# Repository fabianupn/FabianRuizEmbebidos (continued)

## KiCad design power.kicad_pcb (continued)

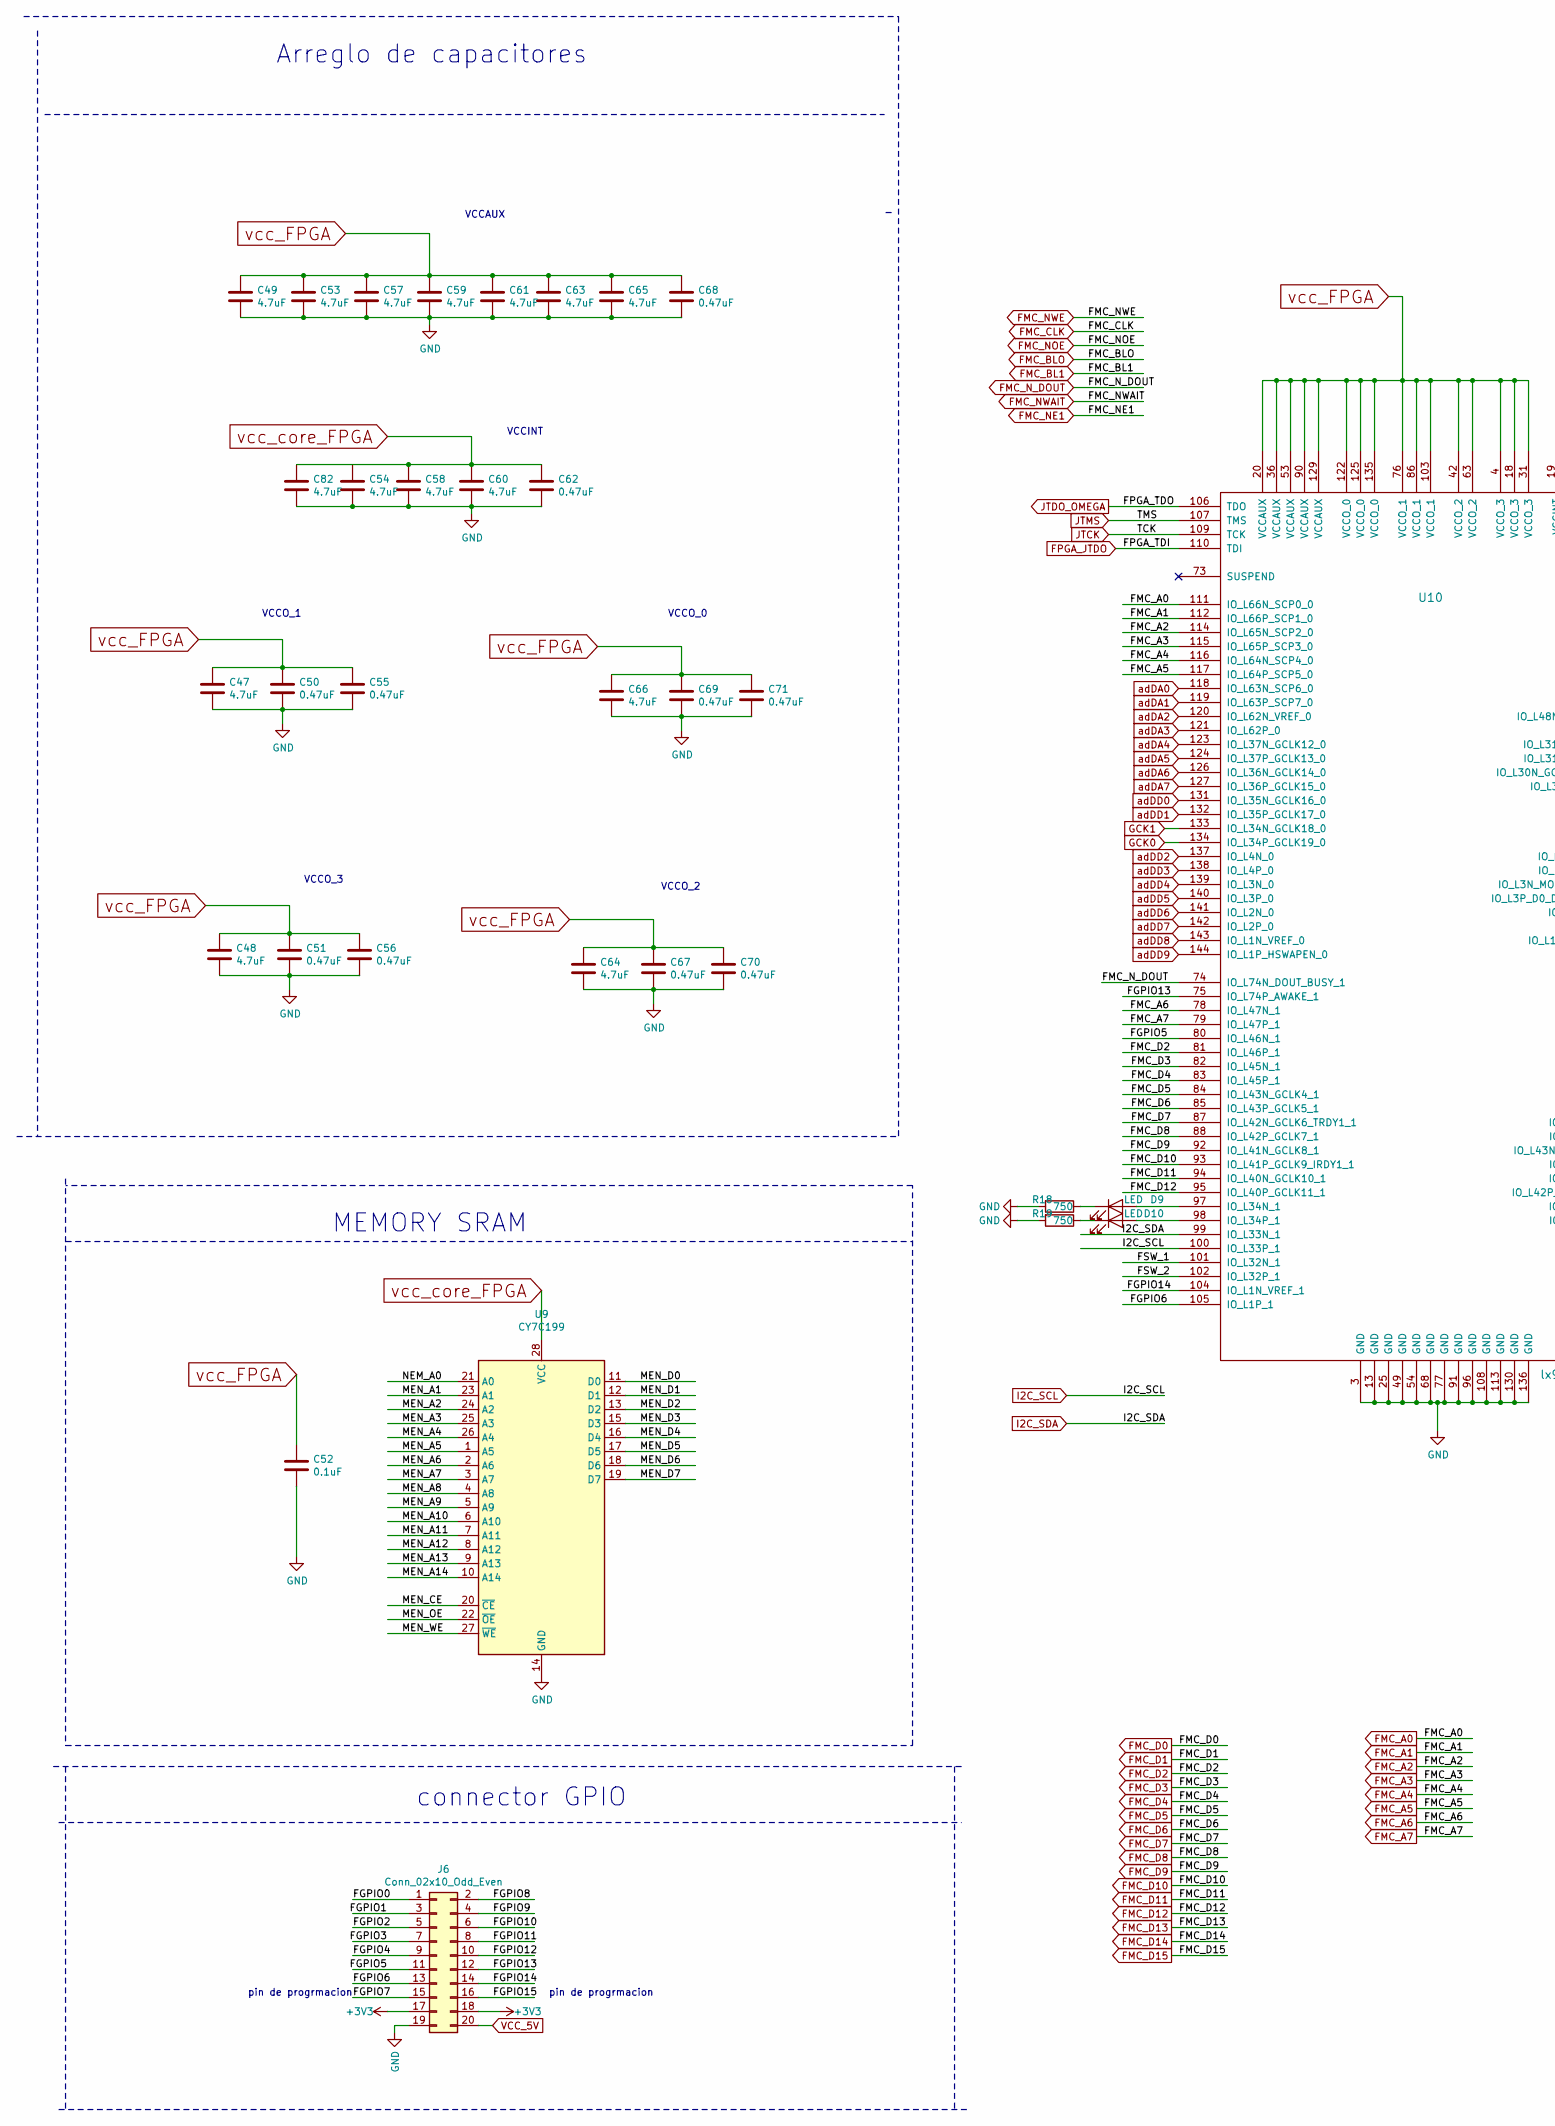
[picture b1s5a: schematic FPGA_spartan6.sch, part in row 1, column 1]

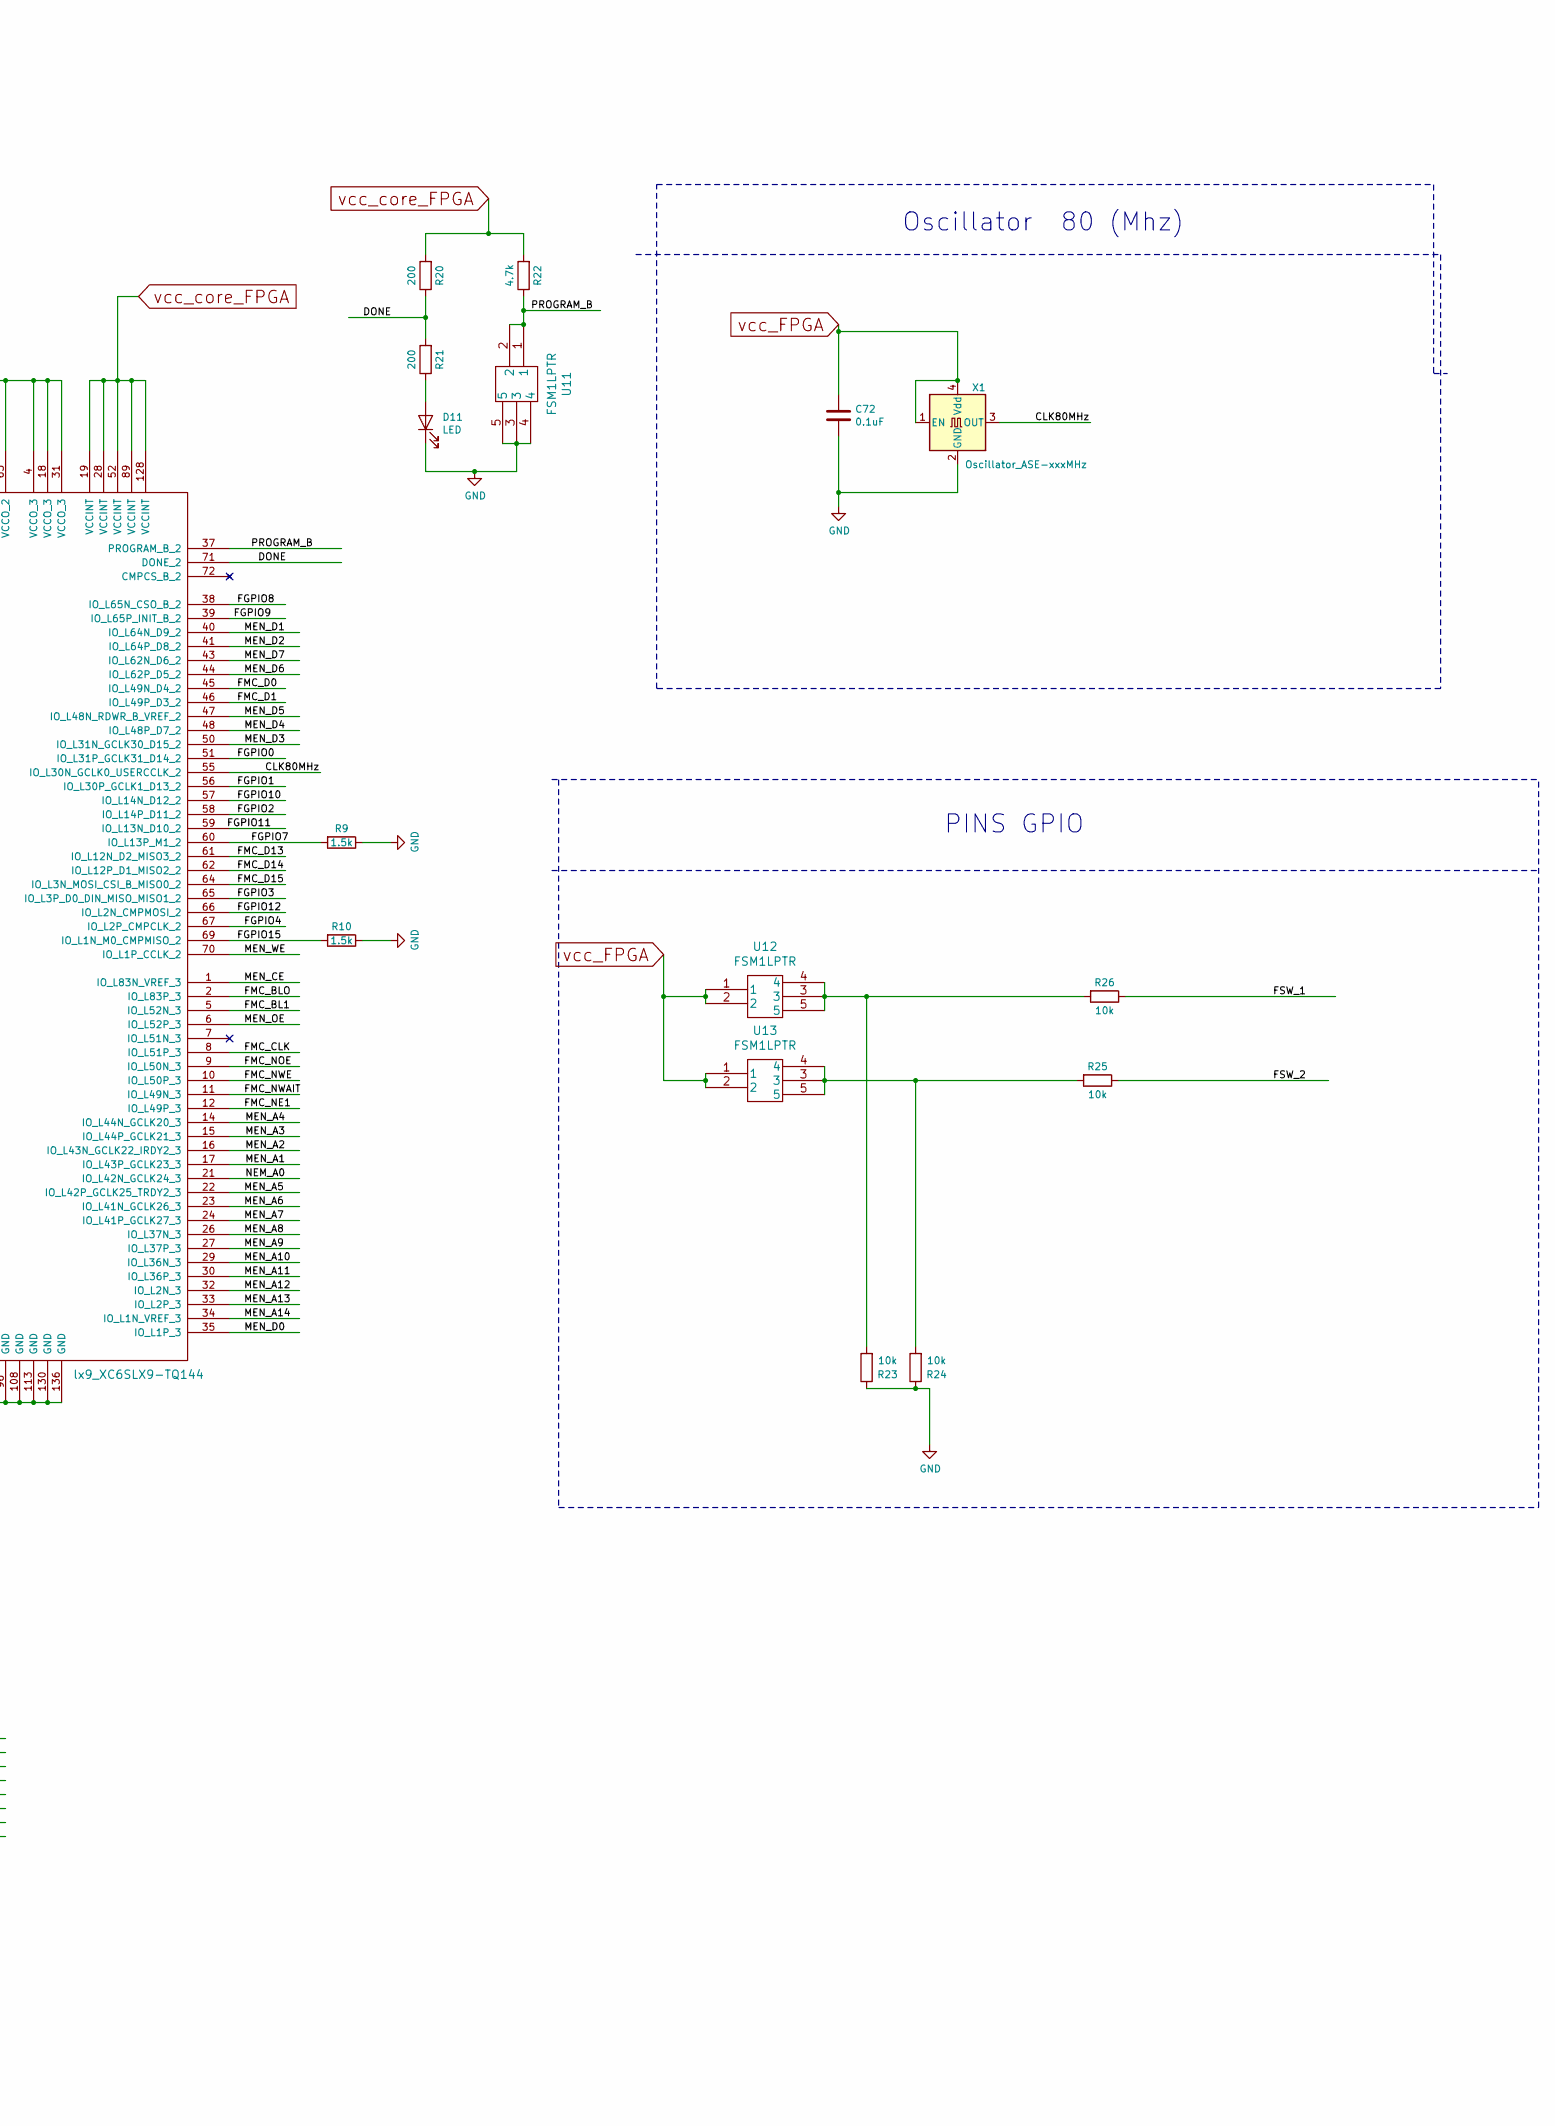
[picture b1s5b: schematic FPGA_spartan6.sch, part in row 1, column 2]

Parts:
C47, C48, C49, C53, C54, C57, C58, C59, C60, C61, C63, C64, C65, C66, C82: 4.7uF; C_0603_1608Metric_Pad1.05x0.95mm_HandSolder
C50, C51, C55, C56, C62, C67, C68, C69, C70, C71: 0.47uF; C_0603_1608Metric_Pad1.05x0.95mm_HandSolder
C52, C72: 0.1uF; C_0603_1608Metric_Pad1.05x0.95mm_HandSolder
D9, D10: LED; LED_0603_1608Metric_Pad1.05x0.95mm_HandSolder; digikey 160-1436-1-ND rojo
D11: LED; LED_0603_1608Metric_Pad1.05x0.95mm_HandSolder; digikey 160-1445-1-ND Naranja
J6: Conn_02x10_Odd_Even; PinHeader_2x10_P2.54mm_Vertical; digikey S6106-ND
R9, R10: 1.5k; R_0603_1608Metric_Pad1.05x0.95mm_HandSolder
R18, R19: 750; R_0603_1608Metric_Pad1.05x0.95mm_HandSolder
R20, R21: 200; R_0603_1608Metric_Pad1.05x0.95mm_HandSolder
R22: 4.7k; R_0603_1608Metric_Pad1.05x0.95mm_HandSolder
R23, R24, R25, R26: 10k; R_0603_1608Metric_Pad1.05x0.95mm_HandSolder
U9: CY7C199; TSOP-I-28_11.8x8mm_P0.55mm; digikey 428-2013-ND
U10: lx9_XC6SLX9-TQ144; LQFP-144_20x20mm_P0.5mm; digiker 122-1745-ND
U11, U12, U13: FSM1LPTR; digikey 450-1756-1-ND
X1: Oscillator_ASE-xxxMHz; Oscillator_SMD_Abracon_ASE-4Pin_3.2x2.5mm_HandSoldering; digikey 535-11114-1-ND

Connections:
/FPGA_spartan6/CLK80MHz: U10.55 (IO_L30N_GCLK0_USERCCLK_2), X1.3 (OUT)
/FPGA_spartan6/DONE: R20.1, R21.2, U10.71 (DONE_2)
/FPGA_spartan6/FGPIO0: J6.1, U10.51 (IO_L31P_GCLK31_D14_2)
/FPGA_spartan6/FGPIO1: J6.3, U10.56 (IO_L30P_GCLK1_D13_2)
/FPGA_spartan6/FGPIO2: J6.5, U10.58 (IO_L14P_D11_2)
/FPGA_spartan6/FGPIO3: J6.7, U10.65 (IO_L3P_D0_DIN_MISO_MISO1_2)
/FPGA_spartan6/FGPIO4: J6.9, U10.67 (IO_L2P_CMPCLK_2)
/FPGA_spartan6/FGPIO5: J6.11, U10.80 (IO_L46N_1)
/FPGA_spartan6/FGPIO6: J6.13, U10.105 (IO_L1P_1)
/FPGA_spartan6/FGPIO7: J6.15, R9.2, U10.60 (IO_L13P_M1_2)
/FPGA_spartan6/FGPIO8: J6.2, U10.38 (IO_L65N_CSO_B_2)
/FPGA_spartan6/FGPIO9: J6.4, U10.39 (IO_L65P_INIT_B_2)
/FPGA_spartan6/FGPIO10: J6.6, U10.57 (IO_L14N_D12_2)
/FPGA_spartan6/FGPIO11: J6.8, U10.59 (IO_L13N_D10_2)
/FPGA_spartan6/FGPIO12: J6.10, U10.66 (IO_L2N_CMPMOSI_2)
/FPGA_spartan6/FGPIO13: J6.12, U10.75 (IO_L74P_AWAKE_1)
/FPGA_spartan6/FGPIO14: J6.14, U10.104 (IO_L1N_VREF_1)
/FPGA_spartan6/FGPIO15: J6.16, R10.2, U10.69 (IO_L1N_M0_CMPMISO_2)
/FPGA_spartan6/FSW_1: R26.1, U10.101 (IO_L32N_1)
/FPGA_spartan6/FSW_2: R25.1, U10.102 (IO_L32P_1)
/FPGA_spartan6/MEN_A1: U9.23 (A1), U10.17 (IO_L43P_GCLK23_3)
/FPGA_spartan6/MEN_A2: U9.24 (A2), U10.16 (IO_L43N_GCLK22_IRDY2_3)
/FPGA_spartan6/MEN_A3: U9.25 (A3), U10.15 (IO_L44P_GCLK21_3)
/FPGA_spartan6/MEN_A4: U9.26 (A4), U10.14 (IO_L44N_GCLK20_3)
/FPGA_spartan6/MEN_A5: U9.1 (A5), U10.22 (IO_L42P_GCLK25_TRDY2_3)
/FPGA_spartan6/MEN_A6: U9.2 (A6), U10.23 (IO_L41N_GCLK26_3)
/FPGA_spartan6/MEN_A7: U9.3 (A7), U10.24 (IO_L41P_GCLK27_3)
/FPGA_spartan6/MEN_A8: U9.4 (A8), U10.26 (IO_L37N_3)
/FPGA_spartan6/MEN_A9: U9.5 (A9), U10.27 (IO_L37P_3)
/FPGA_spartan6/MEN_A10: U9.6 (A10), U10.29 (IO_L36N_3)
/FPGA_spartan6/MEN_A11: U9.7 (A11), U10.30 (IO_L36P_3)
/FPGA_spartan6/MEN_A12: U9.8 (A12), U10.32 (IO_L2N_3)
/FPGA_spartan6/MEN_A13: U9.9 (A13), U10.33 (IO_L2P_3)
/FPGA_spartan6/MEN_A14: U9.10 (A14), U10.34 (IO_L1N_VREF_3)
/FPGA_spartan6/MEN_CE: U9.20 (~CE~), U10.1 (IO_L83N_VREF_3)
/FPGA_spartan6/MEN_D0: U9.11 (D0), U10.35 (IO_L1P_3)
/FPGA_spartan6/MEN_D1: U9.12 (D1), U10.40 (IO_L64N_D9_2)
/FPGA_spartan6/MEN_D2: U9.13 (D2), U10.41 (IO_L64P_D8_2)
/FPGA_spartan6/MEN_D3: U9.15 (D3), U10.50 (IO_L31N_GCLK30_D15_2)
/FPGA_spartan6/MEN_D4: U9.16 (D4), U10.48 (IO_L48P_D7_2)
/FPGA_spartan6/MEN_D5: U9.17 (D5), U10.47 (IO_L48N_RDWR_B_VREF_2)
/FPGA_spartan6/MEN_D6: U9.18 (D6), U10.44 (IO_L62P_D5_2)
/FPGA_spartan6/MEN_D7: U9.19 (D7), U10.43 (IO_L62N_D6_2)
/FPGA_spartan6/MEN_OE: U9.22 (~OE~), U10.6 (IO_L52P_3)
/FPGA_spartan6/MEN_WE: U9.27 (~WE~), U10.70 (IO_L1P_CCLK_2)
/FPGA_spartan6/NEM_A0: U9.21 (A0), U10.21 (IO_L42N_GCLK24_3)
/FPGA_spartan6/PROGRAM_B: R22.1, U10.37 (PROGRAM_B_2), U11.1, U11.2
FMC_A0: U10.111 (IO_L66N_SCP0_0); also elsewhere on the board
FMC_A1: U10.112 (IO_L66P_SCP1_0); also elsewhere on the board
FMC_A2: U10.114 (IO_L65N_SCP2_0); also elsewhere on the board
FMC_A3: U10.115 (IO_L65P_SCP3_0); also elsewhere on the board
FMC_A4: U10.116 (IO_L64N_SCP4_0); also elsewhere on the board
FMC_A5: U10.117 (IO_L64P_SCP5_0); also elsewhere on the board
FMC_A6: U10.78 (IO_L47N_1); also elsewhere on the board
FMC_A7: U10.79 (IO_L47P_1); also elsewhere on the board
FMC_BL1: U10.5 (IO_L52N_3); also elsewhere on the board
FMC_BLO: U10.2 (IO_L83P_3); also elsewhere on the board
FMC_CLK: U10.8 (IO_L51P_3); also elsewhere on the board
FMC_D0: U10.45 (IO_L49N_D4_2); also elsewhere on the board
FMC_D1: U10.46 (IO_L49P_D3_2); also elsewhere on the board
FMC_D2: U10.81 (IO_L46P_1); also elsewhere on the board
FMC_D3: U10.82 (IO_L45N_1); also elsewhere on the board
FMC_D4: U10.83 (IO_L45P_1); also elsewhere on the board
FMC_D5: U10.84 (IO_L43N_GCLK4_1); also elsewhere on the board
FMC_D6: U10.85 (IO_L43P_GCLK5_1); also elsewhere on the board
FMC_D7: U10.87 (IO_L42N_GCLK6_TRDY1_1); also elsewhere on the board
FMC_D8: U10.88 (IO_L42P_GCLK7_1); also elsewhere on the board
FMC_D9: U10.92 (IO_L41N_GCLK8_1); also elsewhere on the board
FMC_D10: U10.93 (IO_L41P_GCLK9_IRDY1_1); also elsewhere on the board
FMC_D11: U10.94 (IO_L40N_GCLK10_1); also elsewhere on the board
FMC_D12: U10.95 (IO_L40P_GCLK11_1); also elsewhere on the board
FMC_D13: U10.61 (IO_L12N_D2_MISO3_2); also elsewhere on the board
FMC_D14: U10.62 (IO_L12P_D1_MISO2_2); also elsewhere on the board
FMC_D15: U10.64 (IO_L3N_MOSI_CSI_B_MISO0_2); also elsewhere on the board
FMC_NE1: U10.12 (IO_L49P_3); also elsewhere on the board
FMC_NOE: U10.9 (IO_L50N_3); also elsewhere on the board
FMC_NWAIT: U10.11 (IO_L49N_3); also elsewhere on the board
FMC_NWE: U10.10 (IO_L50P_3); also elsewhere on the board
FMC_N_DOUT: U10.74 (IO_L74N_DOUT_BUSY_1); also elsewhere on the board
FPGA_JTDO: U10.110 (TDI); also elsewhere on the board
GCK0: U10.134 (IO_L34P_GCLK19_0); also elsewhere on the board
GCK1: U10.133 (IO_L34N_GCLK18_0); also elsewhere on the board
GND: C47.2, C48.2, C49.2, C50.2, C51.2, C52.2, C53.2, C54.2, C55.2, C56.2, C57.2, C58.2, C59.2, C60.2, C61.2, C62.2, C63.2, C64.2, C65.2, C66.2, C67.2, C68.2, C69.2, C70.2, C71.2, C72.2, C82.2, D11.1 (K), J6.19, R9.1, R10.1, R18.2, R19.2, R23.1, R24.1, U9.14 (GND), U10.3 (GND), U10.13 (GND), U10.25 (GND), U10.49 (GND), U10.54 (GND), U10.68 (GND), U10.77 (GND), U10.91 (GND), U10.96 (GND), U10.108 (GND), U10.113 (GND), U10.130 (GND), U10.136 (GND), U11.3, U11.4, U11.5, X1.2 (GND); also elsewhere on the board
I2C_SCL: U10.100 (IO_L33P_1); also elsewhere on the board
I2C_SDA: U10.99 (IO_L33N_1); also elsewhere on the board
JTCK: U10.109 (TCK); also elsewhere on the board
JTDO_OMEGA: U10.106 (TDO); also elsewhere on the board
JTMS: U10.107 (TMS); also elsewhere on the board
unnamed: D9.1 (K), R18.1
unnamed: D9.2 (A), U10.97 (IO_L34N_1)
unnamed: D10.1 (K), R19.1
unnamed: D10.2 (A), U10.98 (IO_L34P_1)
unnamed: D11.2 (A), R21.1
unnamed: R23.2, R26.2, U12.3, U12.4, U12.5
unnamed: R24.2, R25.2, U13.3, U13.4, U13.5
VCC_5V: J6.20; also elsewhere on the board
adDA0: U10.118 (IO_L63N_SCP6_0); also elsewhere on the board
adDA1: U10.119 (IO_L63P_SCP7_0); also elsewhere on the board
adDA2: U10.120 (IO_L62N_VREF_0); also elsewhere on the board
adDA3: U10.121 (IO_L62P_0); also elsewhere on the board
adDA4: U10.123 (IO_L37N_GCLK12_0); also elsewhere on the board
adDA5: U10.124 (IO_L37P_GCLK13_0); also elsewhere on the board
adDA6: U10.126 (IO_L36N_GCLK14_0); also elsewhere on the board
adDA7: U10.127 (IO_L36P_GCLK15_0); also elsewhere on the board
adDD0: U10.131 (IO_L35N_GCLK16_0); also elsewhere on the board
adDD1: U10.132 (IO_L35P_GCLK17_0); also elsewhere on the board
adDD2: U10.137 (IO_L4N_0); also elsewhere on the board
adDD3: U10.138 (IO_L4P_0); also elsewhere on the board
adDD4: U10.139 (IO_L3N_0); also elsewhere on the board
adDD5: U10.140 (IO_L3P_0); also elsewhere on the board
adDD6: U10.141 (IO_L2N_0); also elsewhere on the board
adDD7: U10.142 (IO_L2P_0); also elsewhere on the board
adDD8: U10.143 (IO_L1N_VREF_0); also elsewhere on the board
adDD9: U10.144 (IO_L1P_HSWAPEN_0); also elsewhere on the board
vcc_FPGA: C47.1, C48.1, C49.1, C50.1, C51.1, C52.1, C53.1, C55.1, C56.1, C57.1, C59.1, C61.1, C63.1, C64.1, C65.1, C66.1, C67.1, C68.1, C69.1, C70.1, C71.1, C72.1, J6.17, J6.18, U10.4 (VCCO_3), U10.18 (VCCO_3), U10.20 (VCCAUX), U10.31 (VCCO_3), U10.36 (VCCAUX), U10.42 (VCCO_2), U10.53 (VCCAUX), U10.63 (VCCO_2), U10.76 (VCCO_1), U10.86 (VCCO_1), U10.90 (VCCAUX), U10.103 (VCCO_1), U10.122 (VCCO_0), U10.125 (VCCO_0), U10.129 (VCCAUX), U10.135 (VCCO_0), U12.1, U12.2, U13.1, U13.2, X1.1 (EN), X1.4 (Vdd); also elsewhere on the board
vcc_core_FPGA: C54.1, C58.1, C60.1, C62.1, C82.1, R20.2, R22.2, U9.28 (VCC), U10.19 (VCCINT), U10.28 (VCCINT), U10.52 (VCCINT), U10.89 (VCCINT), U10.128 (VCCINT); also elsewhere on the board

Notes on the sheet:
Arreglo de capacitores
Oscillator 80 (Mhz)
MEMORY SRAM
PINS GPIO
connector GPIO
VCCAUX
VCCINT
VCCO_0
VCCO_1
VCCO_3
VCCO_2
pin de progrmacion

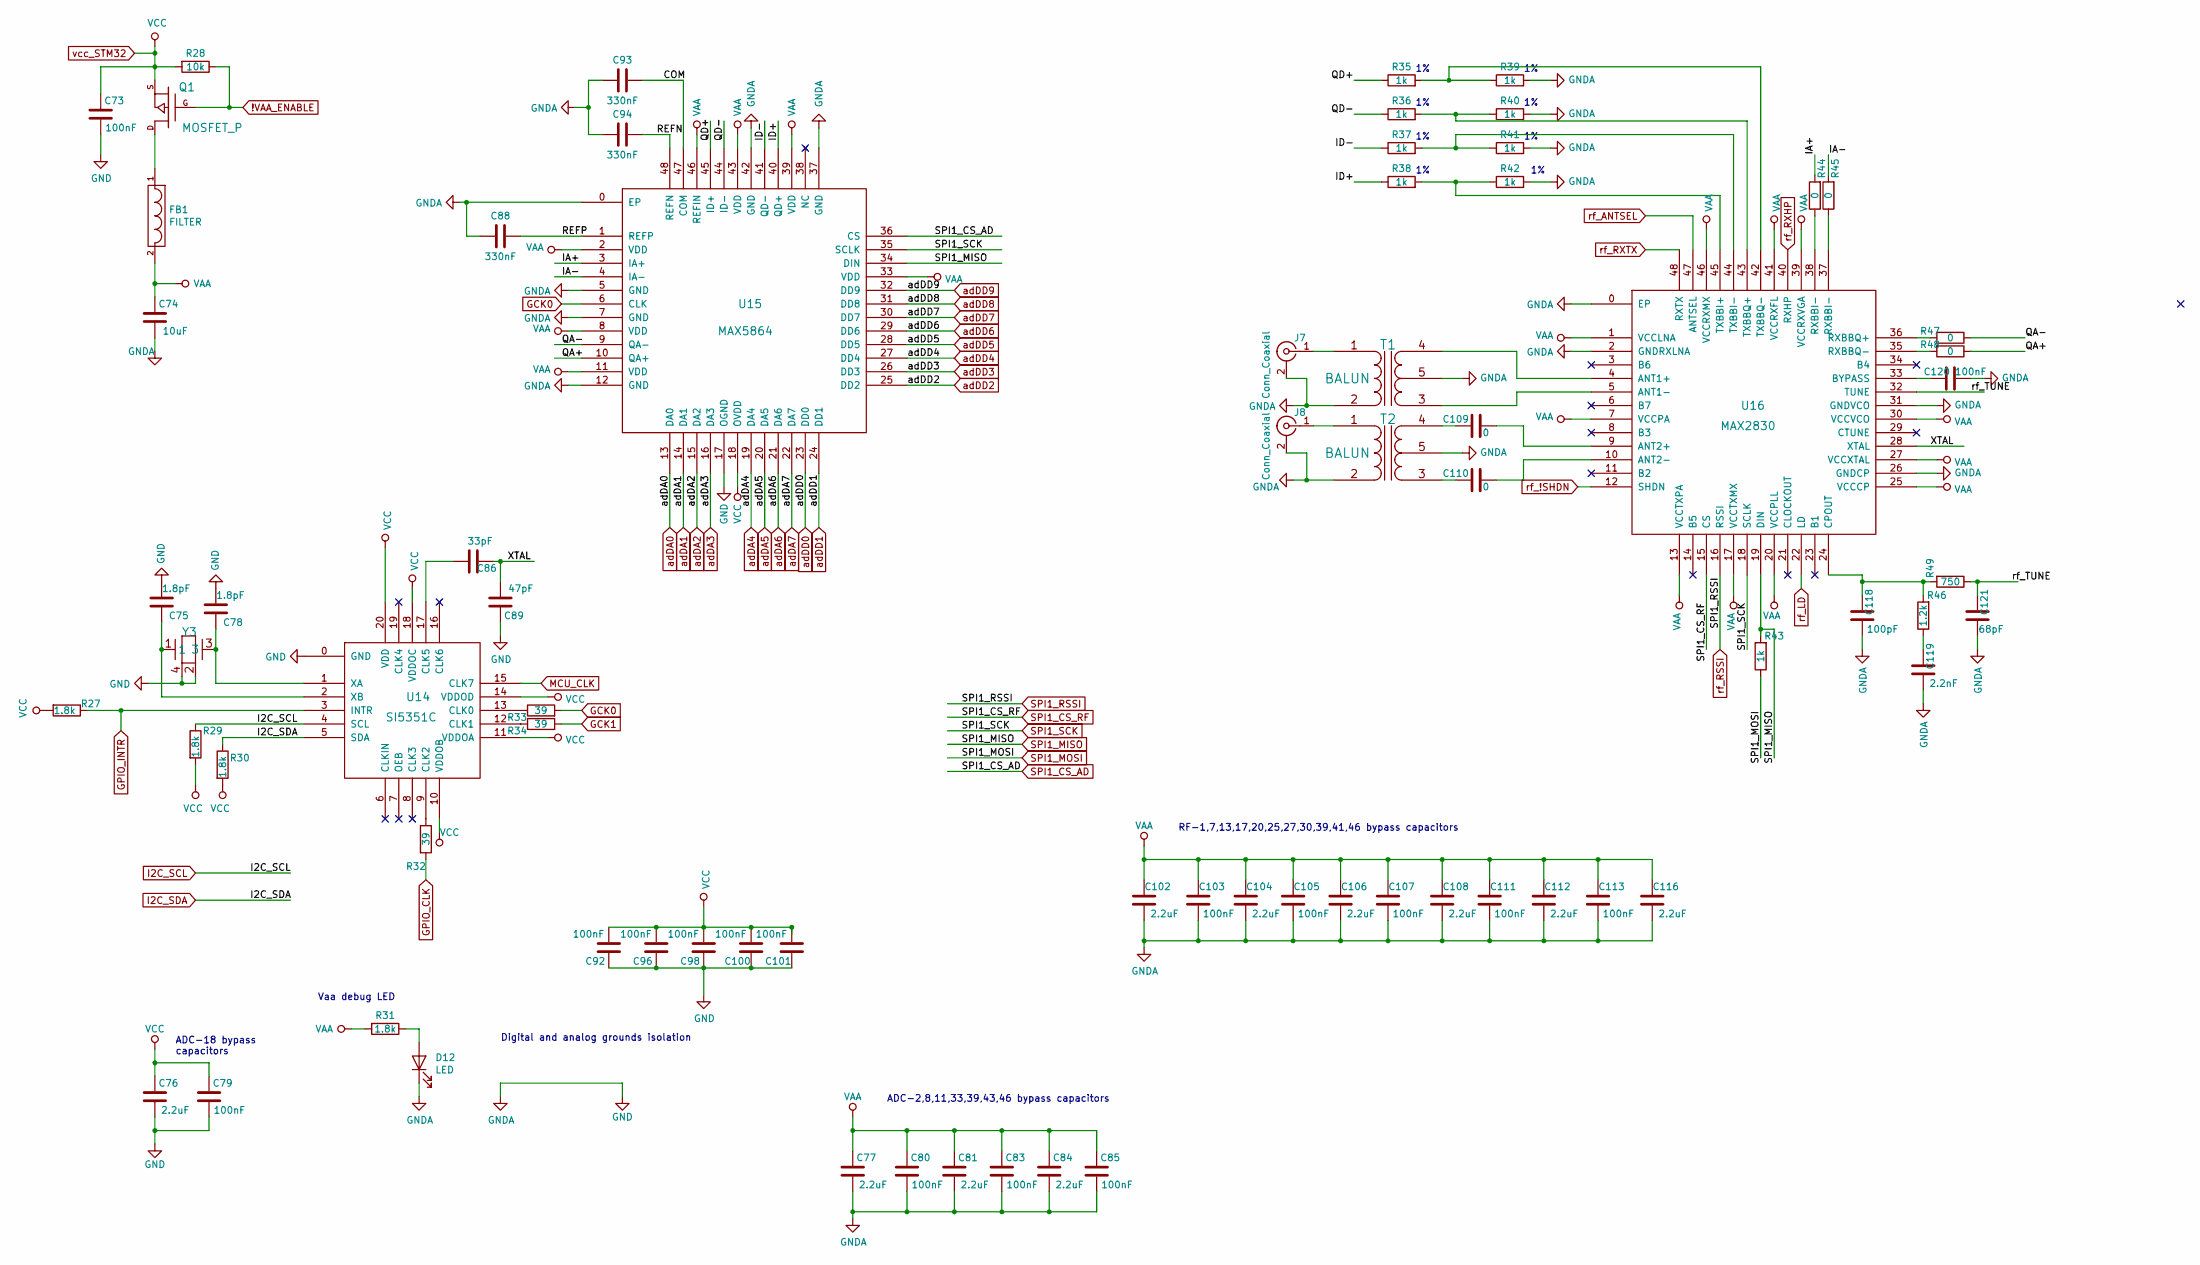
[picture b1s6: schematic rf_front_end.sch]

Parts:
C73, C79, C80, C83, C85, C92, C96, C98, C100, C101, C103, C105, C107, C111, C113, C120: 100nF; C_0603_1608Metric_Pad1.05x0.95mm_HandSolder
C74: 10uF; C_0603_1608Metric_Pad1.05x0.95mm_HandSolder
C75, C78: 1.8pF; C_0603_1608Metric_Pad1.05x0.95mm_HandSolder; digikey 1276-2218-1-ND
C76, C77, C81, C84, C102, C104, C106, C108, C112, C116: 2.2uF; C_0603_1608Metric_Pad1.05x0.95mm_HandSolder
C86: 33pF; C_0603_1608Metric_Pad1.05x0.95mm_HandSolder; digikey 1276-1070-1-ND
C88, C93, C94: 330nF; C_0603_1608Metric_Pad1.05x0.95mm_HandSolder
C89: 47pF; C_0603_1608Metric_Pad1.05x0.95mm_HandSolder
C109, C110: 0; C_0603_1608Metric_Pad1.05x0.95mm_HandSolder; digikey RMCF0603ZT0R00CT-ND
C118: 100pF; C_0603_1608Metric_Pad1.05x0.95mm_HandSolder
C119: 2.2nF; C_0603_1608Metric_Pad1.05x0.95mm_HandSolder
C121: 68pF; C_0603_1608Metric_Pad1.05x0.95mm_HandSolder
D12: LED; LED_0603_1608Metric_Pad1.05x0.95mm_HandSolder
FB1: FILTER; L_0805_2012Metric_Pad1.15x1.40mm_HandSolder; digikey BLM21PG221SN1D
J7, J8: Conn_Coaxial; TAOGLAS_EMPCB.SMAFSTJ.B.HT
Q1: MOSFET_P; SOT103P240X110-3N; digikey DMP2305UDICT-ND
R27, R29, R30, R31: 1.8k; R_0603_1608Metric_Pad1.05x0.95mm_HandSolder
R28: 10k; R_0603_1608Metric_Pad1.05x0.95mm_HandSolder
R32, R34: 39; R_0603_1608Metric_Pad1.05x0.95mm_HandSolder; DIGIKEY 311-39.0HRCT-ND
R33: 39; R_0603_1608Metric_Pad1.05x0.95mm_HandSolder; DIGIKEY RMSF0402JT39R0CT-ND
R35, R36, R37, R38, R39, R40, R41, R42, R43: 1k; R_0603_1608Metric_Pad1.05x0.95mm_HandSolder
R44, R45, R48: 0; R_0603_1608Metric_Pad1.05x0.95mm_HandSolder
R46: 1.2k; R_0603_1608Metric_Pad1.05x0.95mm_HandSolder
R47: 0; R_0603_1608Metric_Pad1.05x0.95mm_HandSolder; digikey RMCF0402ZT0R00CT-ND
R49: 750; R_0603_1608Metric_Pad1.05x0.95mm_HandSolder
T1, T2: BALUN; HHM1711E1; digikey 445-172632-1-ND
U14: SI5351C; QFN50P300X300X60-21N; digikey 336-5160-1-ND
U15: MAX5864; MAX5864ETM&plus_
U16: MAX2830; MAX2830ETM&plus_
Y3: ABM8G-25.000MHZ-B4Y-T; GSG-XTAL3.2x2.5mm; digikey ABM8-25.000MHZ-10-D1G-T

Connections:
!VAA_ENABLE: Q1.G, R28.1; also elsewhere on the board
/rf_front_end/COM: C93.1, U15.47 (COM)
/rf_front_end/IA+: R44.2, U15.3 (IA+)
/rf_front_end/IA-: R45.2, U15.4 (IA-)
/rf_front_end/ID+: R38.1, U15.40 (QD+)
/rf_front_end/ID-: R37.1, U15.41 (QD-)
/rf_front_end/QA+: R48.1, U15.10 (QA+)
/rf_front_end/QA-: R47.1, U15.9 (QA-)
/rf_front_end/QD+: R35.1, U15.45 (ID+)
/rf_front_end/QD-: R36.1, U15.44 (ID-)
/rf_front_end/REFN: C94.1, U15.48 (REFN)
/rf_front_end/REFP: C88.1, U15.1 (REFP)
/rf_front_end/XTAL: C86.2, C89.2, U16.28 (XTAL)
/rf_front_end/rf_TUNE: C121.1, R49.1, U16.32 (TUNE)
GCK0: R33.2, U15.6 (CLK); also elsewhere on the board
GCK1: R34.2; also elsewhere on the board
GND: C73.2, C74.2, C75.1, C76.2, C77.2, C78.1, C79.2, C80.2, C81.2, C83.2, C84.2, C85.2, C88.2, C89.1, C92.1, C93.2, C94.2, C96.1, C98.1, C100.1, C101.1, C102.2, C103.2, C104.2, C105.2, C106.2, C107.2, C108.2, C111.2, C112.2, C113.2, C116.2, C118.2, C119.2, C120.2, C121.2, D12.1 (K), J7.2 (Ext), J8.2 (Ext), R39.2, R40.2, R41.2, R42.2, T1.2 (S2), T1.5 (PM), T2.2 (S2), T2.5 (PM), U14.0 (GND), U15.0 (EP), U15.5 (GND), U15.7 (GND), U15.12 (GND), U15.17 (OGND), U15.37 (GND), U15.42 (GND), U16.0 (EP), U16.2 (GNDRXLNA), U16.26 (GNDCP), U16.31 (GNDVCO), Y3.2, Y3.4; also elsewhere on the board
GPIO_CLK: R32.2; also elsewhere on the board
GPIO_INTR: R27.1, U14.3 (INTR); also elsewhere on the board
I2C_SCL: R29.1, U14.4 (SCL); also elsewhere on the board
I2C_SDA: R30.1, U14.5 (SDA); also elsewhere on the board
MCU_CLK: U14.15 (CLK7); also elsewhere on the board
unnamed: C75.2, U14.2 (XB), Y3.1
unnamed: C78.2, U14.1 (XA), Y3.3
unnamed: C86.1, U14.17 (CLK5)
unnamed: C109.1, T2.4 (PR2)
unnamed: C109.2, U16.9 (ANT2+)
unnamed: C110.1, T2.3 (PR1)
unnamed: C110.2, U16.10 (ANT2-)
unnamed: C118.1, R46.2, R49.2, U16.24 (CPOUT)
unnamed: C119.1, R46.1
unnamed: C120.1, U16.33 (BYPASS)
unnamed: D12.2 (A), R31.1
unnamed: FB1.1, Q1.D
unnamed: J7.1 (In), T1.1 (S1)
unnamed: J8.1 (In), T2.1 (S1)
unnamed: R32.1, U14.9 (CLK2)
unnamed: R33.1, U14.13 (CLK0)
unnamed: R34.1, U14.12 (CLK1)
unnamed: R35.2, R39.1, U16.42 (TXBBQ-)
unnamed: R36.2, R40.1, U16.43 (TXBBQ+)
unnamed: R37.2, R41.1, U16.44 (TXBBI-)
unnamed: R38.2, R42.1, U16.45 (TXBBI+)
unnamed: R44.1, U16.38 (RXBBI-)
unnamed: R45.1, U16.37 (RXBBI-)
unnamed: R47.2, U16.36 (RXBBQ+)
unnamed: R48.2, U16.35 (RXBBQ-)
unnamed: T1.3 (PR1), U16.5 (ANT1-)
unnamed: T1.4 (PR2), U16.4 (ANT1+)
SPI1_CS_AD: U15.36 (CS); also elsewhere on the board
SPI1_CS_RF: U16.15 (CS); also elsewhere on the board
SPI1_MISO: R43.2, U15.34 (DIN), U16.19 (DIN); also elsewhere on the board
SPI1_MOSI: R43.1; also elsewhere on the board
SPI1_RSSI: U16.16 (RSSI); also elsewhere on the board
SPI1_SCK: U15.35 (SCLK), U16.18 (SCLK); also elsewhere on the board
VAA: C74.1, C77.1, C80.1, C81.1, C83.1, C84.1, C85.1, C102.1, C103.1, C104.1, C105.1, C106.1, C107.1, C108.1, C111.1, C112.1, C113.1, C116.1, FB1.2, R31.2, U15.2 (VDD), U15.8 (VDD), U15.11 (VDD), U15.33 (VDD), U15.39 (VDD), U15.43 (VDD), U15.46 (REFIN), U16.1 (VCCLNA), U16.7 (VCCPA), U16.13 (VCCTXPA), U16.17 (VCCTXMX), U16.20 (VCCPLL), U16.25 (VCCCP), U16.27 (VCCXTAL), U16.30 (VCCVCO), U16.39 (VCCRXVGA), U16.41 (VCCRXFL), U16.46 (VCCRXMX)
adDA0: U15.13 (DA0); also elsewhere on the board
adDA1: U15.14 (DA1); also elsewhere on the board
adDA2: U15.15 (DA2); also elsewhere on the board
adDA3: U15.16 (DA3); also elsewhere on the board
adDA4: U15.19 (DA4); also elsewhere on the board
adDA5: U15.20 (DA5); also elsewhere on the board
adDA6: U15.21 (DA6); also elsewhere on the board
adDA7: U15.22 (DA7); also elsewhere on the board
adDD0: U15.23 (DD0); also elsewhere on the board
adDD1: U15.24 (DD1); also elsewhere on the board
adDD2: U15.25 (DD2); also elsewhere on the board
adDD3: U15.26 (DD3); also elsewhere on the board
adDD4: U15.27 (DD4); also elsewhere on the board
adDD5: U15.28 (DD5); also elsewhere on the board
adDD6: U15.29 (DD6); also elsewhere on the board
adDD7: U15.30 (DD7); also elsewhere on the board
adDD8: U15.31 (DD8); also elsewhere on the board
adDD9: U15.32 (DD9); also elsewhere on the board
rf_!SHDN: U16.12 (SHDN); also elsewhere on the board
rf_ANTSEL: U16.47 (ANTSEL); also elsewhere on the board
rf_LD: U16.22 (LD); also elsewhere on the board
rf_RXHP: U16.40 (RXHP); also elsewhere on the board
rf_RXTX: U16.48 (RXTX); also elsewhere on the board
vcc_STM32: C73.1, C76.1, C79.1, C92.2, C96.2, C98.2, C100.2, C101.2, Q1.S, R27.2, R28.2, R29.2, R30.2, U14.10 (VDDOB), U14.11 (VDDOA), U14.14 (VDDOD), U14.18 (VDDOC), U14.20 (VDD), U15.18 (OVDD); also elsewhere on the board

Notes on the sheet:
ADC-18 bypass capacitors
ADC-2,8,11,33,39,43,46 bypass capacitors
Vaa debug LED
Digital and analog grounds isolation
RF-1,7,13,17,20,25,27,30,39,41,46 bypass capacitors

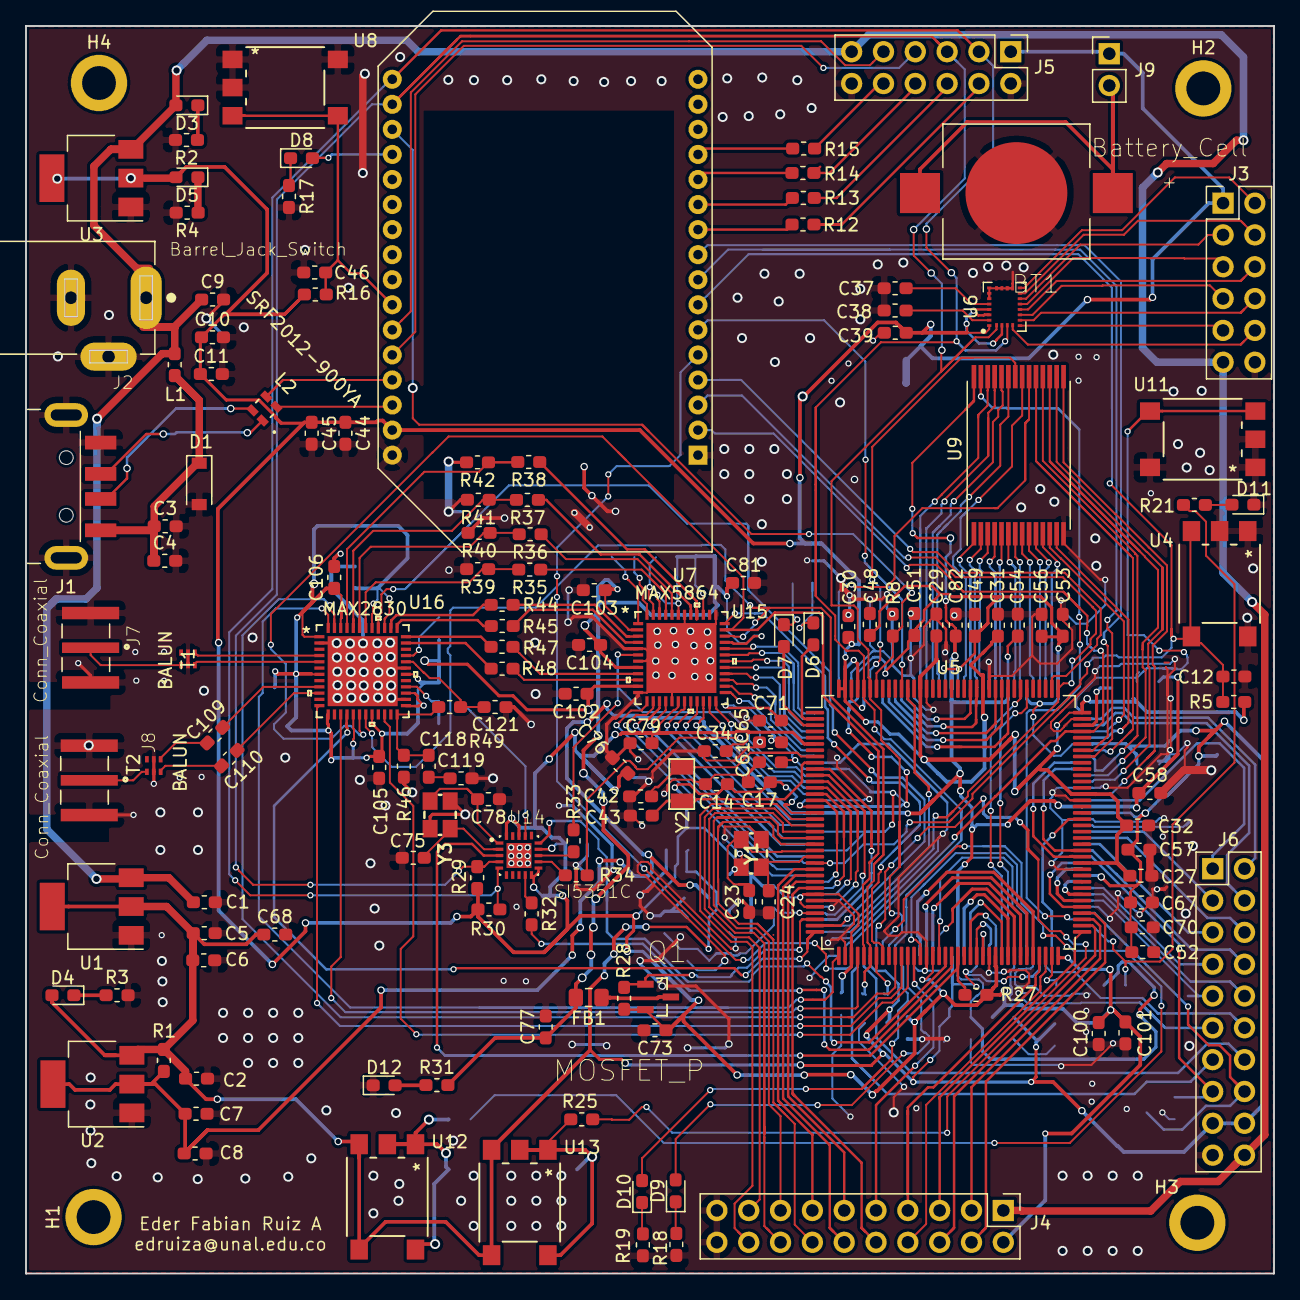
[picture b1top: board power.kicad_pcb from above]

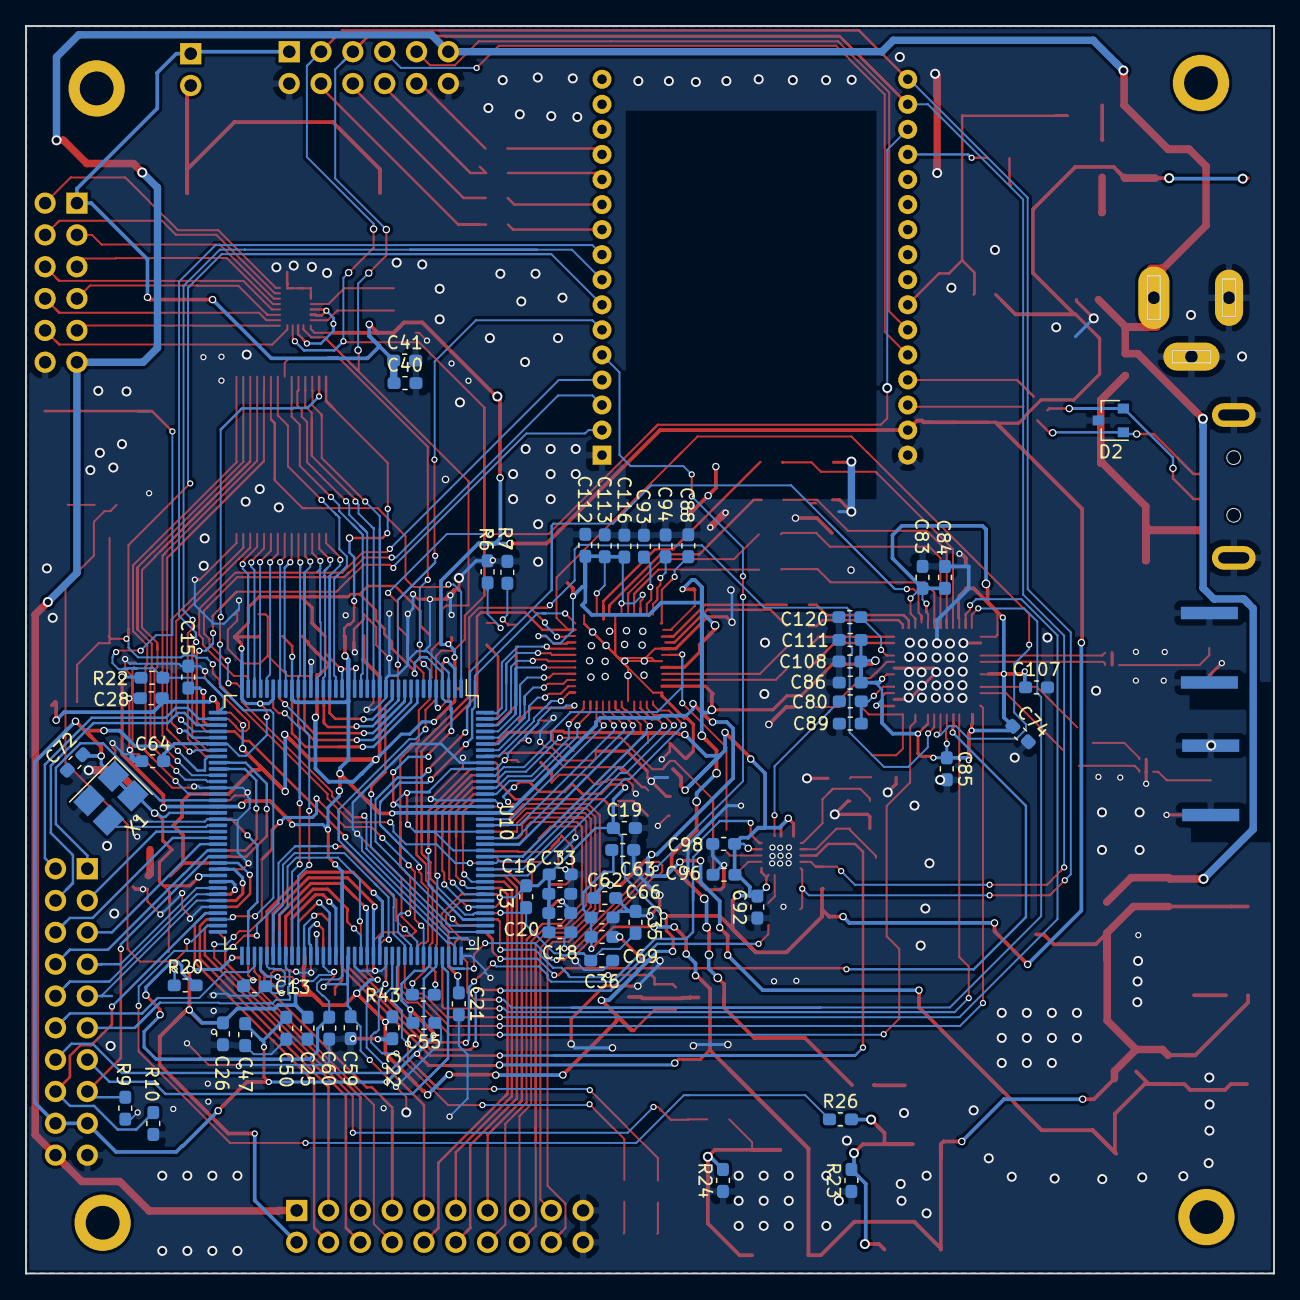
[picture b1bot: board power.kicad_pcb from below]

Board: 2 copper layers, 99.6 x 99.6 mm, 213 parts (61 on the bottom side), 239 nets.

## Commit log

2019-05-16 asignacion pines de control
2019-05-27 retoque casi finales
2019-05-29 diseño de esquematico
2019-06-01 diseño de esquematico fm
2019-06-04 diseño de esquematico CASI FINAL
2019-06-06 diseño de esquematico arreglo de flechas rojas
2019-06-06 Listo solo falta poner nombre
2019-07-23 programacion luego del diseño del embebido
2019-07-24 elimivar xc3sprog que no se necesitan
2019-07-25 archivos necesrios dentro de la onion
2019-07-26 chibiOS modificado
